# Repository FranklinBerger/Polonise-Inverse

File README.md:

# Calculatrice Polonaise Inversse

<p><strong>/!\ Projet en cours de développement vers une verssion stable et correctement doccumentée /!\</strong></p>

Commencé dans le cadre d'un mois de découverte de l'électronique, ce projet consiste en une calculatrice avec [notation en polonaise inversse](https://fr.wikipedia.org/wiki/Notation_polonaise_inverse) dont le hardware est propice à la découverte et l'initiation à l'électronique, soit:
* Montage
* Développement
* Mesures & Dépannage
* Programation

Basée sur ESP32 et dévelopée sur un firware [Micropython](https://github.com/micropython), elle est propice à une compréhenssion de sa structure fondamentale et à des réalisations pratique très rapidement

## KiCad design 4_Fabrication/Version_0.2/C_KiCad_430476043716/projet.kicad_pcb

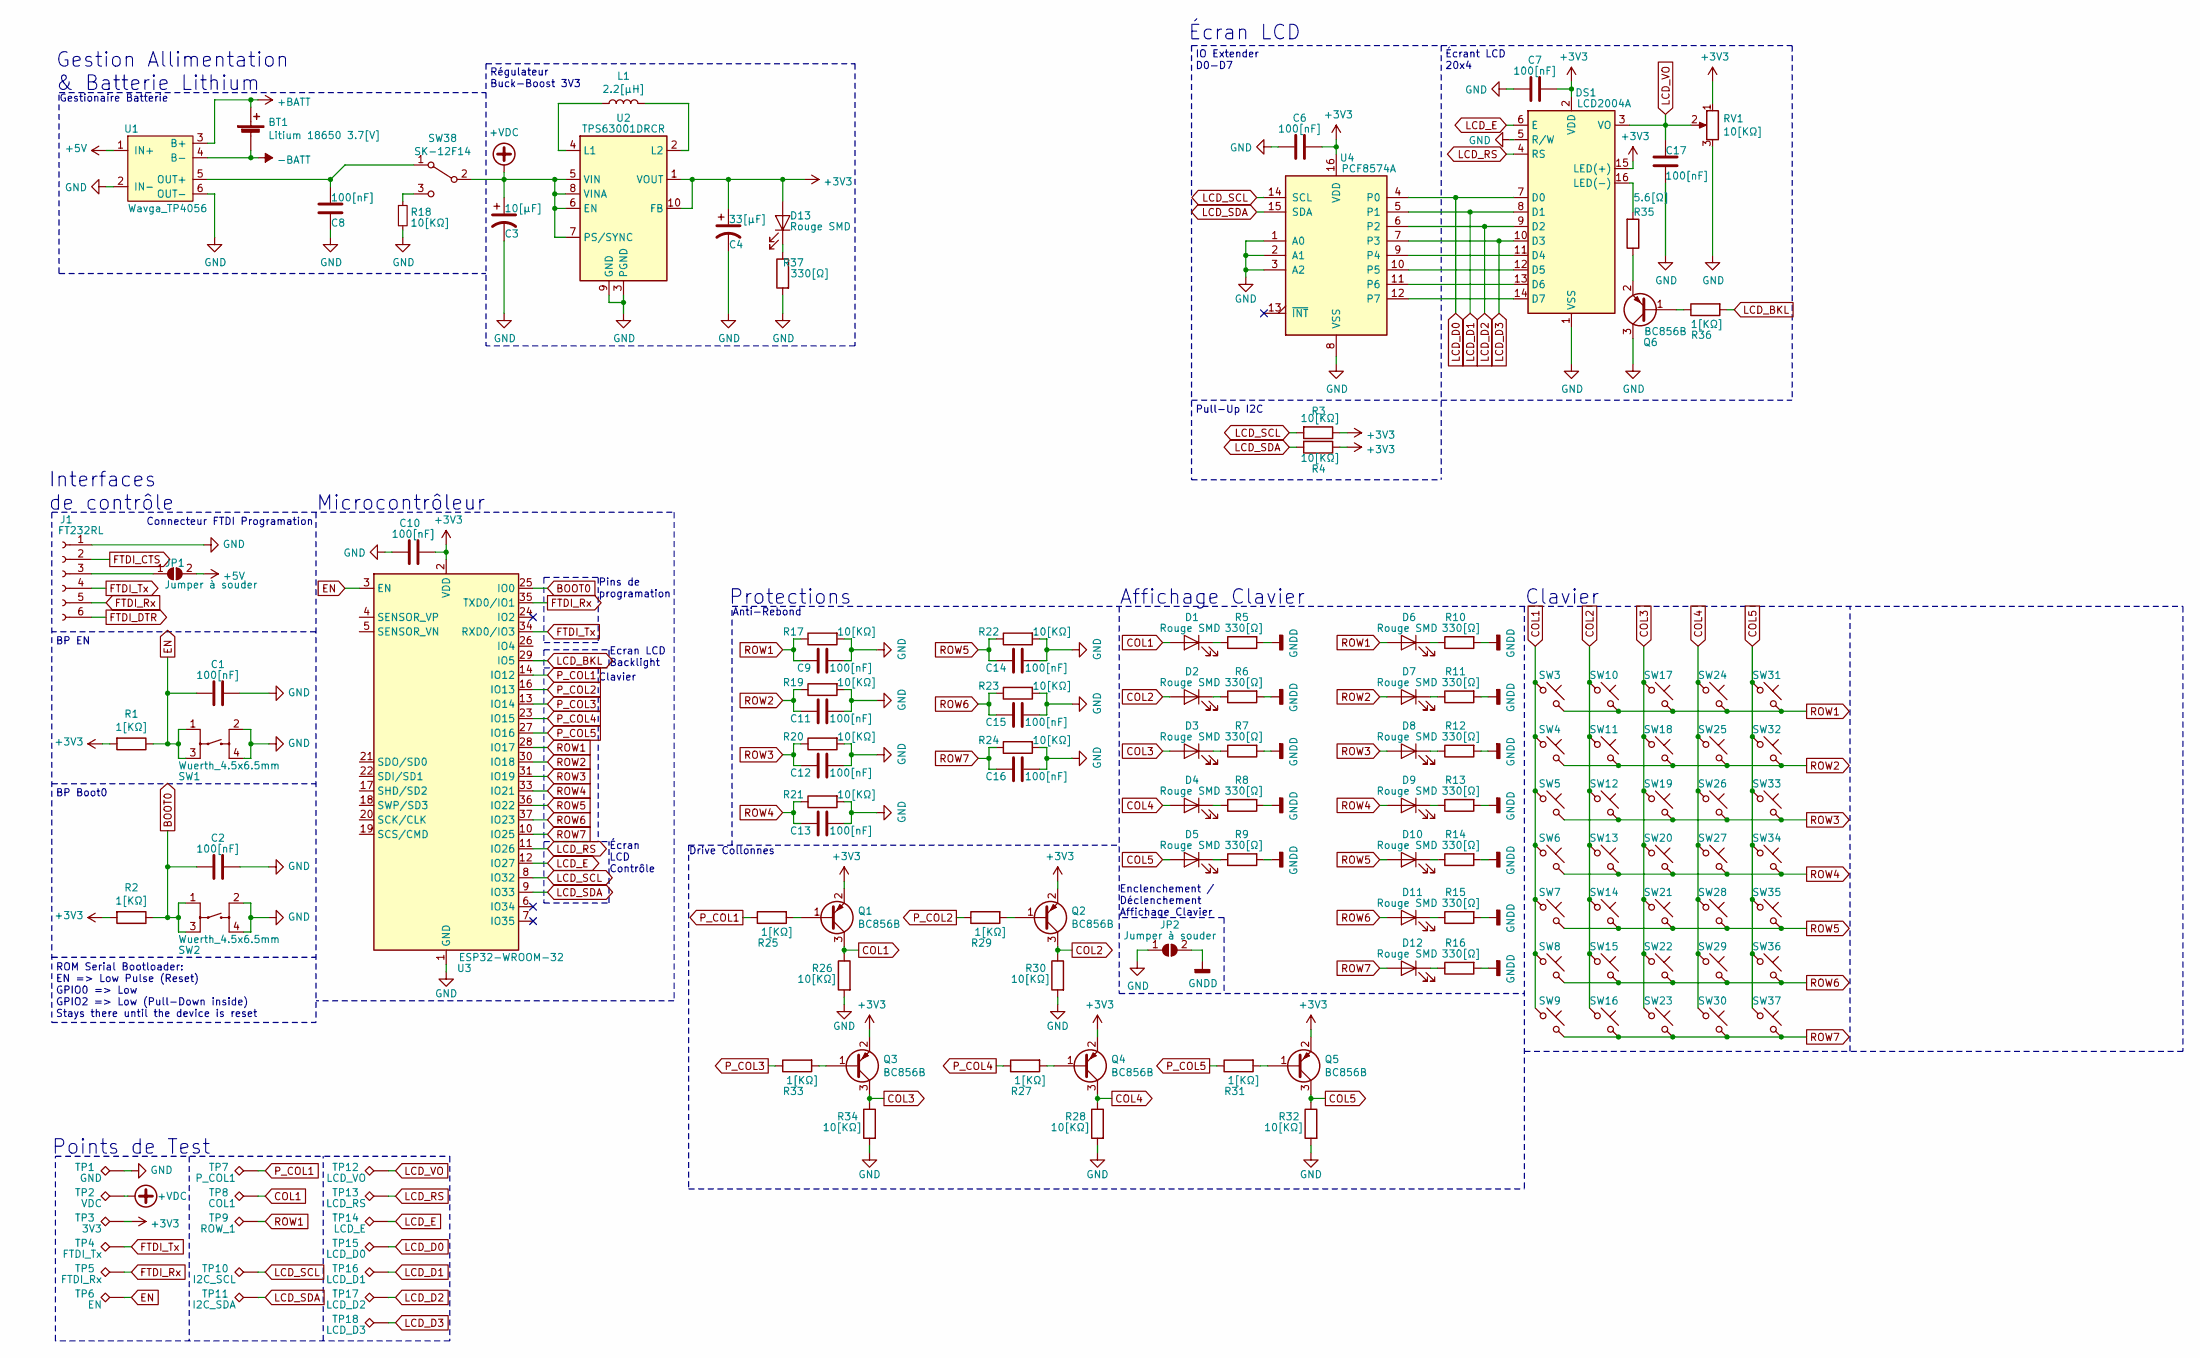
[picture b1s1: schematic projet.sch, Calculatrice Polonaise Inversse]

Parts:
BT1: Litium 18650 3.7[V]; BatteryHolder_Aliexpress_XZT_18650
C1, C2, C6, C7, C8, C9, C10, C11, C12, C13, C14, C15, C16, C17: 100[nF]; C_1206_3216Metric_Pad1.42x1.75mm_HandSolder
C3: 10[μF]; C_1206_3216Metric_Pad1.42x1.75mm_HandSolder
C4: 33[μF]; C_1206_3216Metric_Pad1.42x1.75mm_HandSolder
D1, D2, D3, D4, D5, D6, D7, D8, D9, D10, D11, D12, D13: Rouge SMD; LED_1206_3216Metric_ReverseMount_Hole1.8x2.4mm
DS1: LCD2004A; LCD2004A_TOP
J1: FT232RL; PinSocket_1x06_P2.54mm_Horizontal
JP1, JP2: Jumper à souder; SolderJumper-2_P1.3mm_Open_TrianglePad1.0x1.5mm
L1: 2.2[μH]; L_Taiyo-Yuden_NR-24xx_HandSoldering
Q1, Q2, Q3, Q4, Q5, Q6: BC856B; SOT-23_Handsoldering
R1, R2, R25, R27, R29, R31, R33, R36: 1[KΩ]; R_1206_3216Metric_Pad1.42x1.75mm_HandSolder
R3, R4, R17, R18, R19, R20, R21, R22, R23, R24, R26, R28, R30, R32, R34: 10[KΩ]; R_1206_3216Metric_Pad1.42x1.75mm_HandSolder
R5, R6, R7, R8, R9, R10, R11, R12, R13, R14, R15, R16, R37: 330[Ω]; R_1206_3216Metric_Pad1.42x1.75mm_HandSolder
R35: 5.6[Ω]; R_1206_3216Metric_Pad1.42x1.75mm_HandSolder
RV1: 10[KΩ]; Potentiometer_Bourns_3224J_Horizontal
SW1, SW2: Wuerth_4.5x6.5mm; SW_Wuerth_6.5x4.5mm
SW3, SW4, SW5, SW6, SW7, SW8, SW9, SW10, SW11, SW12, SW13, SW14, SW15, SW16, SW17, SW18, SW19, SW20, SW21, SW22, SW23, SW24, SW25, SW26, SW27, SW28, SW29, SW30, SW31, SW32, SW33, SW34, SW35, SW36, SW37: G77; SW_PUSH-12mm_Wuerth-430476085716
SW38: SK-12F14; SW_CuK_OS102011MA1QN1_SPDT_Angled
TP1: GND; TestPoint_Pad_1.5x1.5mm
TP2: VDC; TestPoint_Pad_1.5x1.5mm
TP3: 3V3; TestPoint_Pad_1.5x1.5mm
TP4: FTDI_Tx; TestPoint_Pad_1.5x1.5mm
TP5: FTDI_Rx; TestPoint_Pad_1.5x1.5mm
TP6: EN; TestPoint_Pad_1.5x1.5mm
TP7: P_COL1; TestPoint_Pad_1.5x1.5mm
TP8: COL1; TestPoint_Pad_1.5x1.5mm
TP9: ROW_1; TestPoint_Pad_1.5x1.5mm
TP10: I2C_SCL; TestPoint_Pad_1.5x1.5mm
TP11: I2C_SDA; TestPoint_Pad_1.5x1.5mm
TP12: LCD_VO; TestPoint_Pad_1.5x1.5mm
TP13: LCD_RS; TestPoint_Pad_1.5x1.5mm
TP14: LCD_E; TestPoint_Pad_1.5x1.5mm
TP15: LCD_D0; TestPoint_Pad_1.5x1.5mm
TP16: LCD_D1; TestPoint_Pad_1.5x1.5mm
TP17: LCD_D2; TestPoint_Pad_1.5x1.5mm
TP18: LCD_D3; TestPoint_Pad_1.5x1.5mm
U1: Wavga_TP4056; Wavgat_TP4056
U2: TPS63001DRCR; Texas_DRC0010J_ThermalVias
U3: ESP32-WROOM-32
U4: PCF8574A; SOIC-16W_7.5x10.3mm_P1.27mm

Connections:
+3V3: C4.1, C6.2, C7.2, C10.2, D13.2 (A), DS1.2 (VDD), DS1.15 (LED(+)), Q1.2 (E), Q2.2 (E), Q3.2 (E), Q4.2 (E), Q5.2 (E), R1.2, R2.2, R3.1, R4.1, RV1.1, TP3.1, U2.1 (VOUT), U2.10 (FB), U3.2 (VDD), U4.16 (VDD)
+5V: JP1.2 (B), U1.1 (IN+)
+BATT: BT1.1 (+), U1.3 (B+)
+VDC: C3.1, SW38.2 (B), TP2.1, U2.5 (VIN), U2.6 (EN), U2.7 (PS/SYNC), U2.8 (VINA)
-BATT: BT1.2 (-), U1.4 (B-)
BOOT0: C2.1, R2.1, SW2.1, SW2.3, U3.25 (IO0)
COL1: D1.2 (A), Q1.3 (C), R26.1, SW3.1, SW4.1, SW5.1, SW6.1, SW7.1, SW8.1, SW9.1, TP8.1
COL2: D2.2 (A), Q2.3 (C), R30.1, SW10.1, SW11.1, SW12.1, SW13.1, SW14.1, SW15.1, SW16.1
COL3: D3.2 (A), Q3.3 (C), R34.1, SW17.1, SW18.1, SW19.1, SW20.1, SW21.1, SW22.1, SW23.1
COL4: D4.2 (A), Q4.3 (C), R28.1, SW24.1, SW25.1, SW26.1, SW27.1, SW28.1, SW29.1, SW30.1
COL5: D5.2 (A), Q5.3 (C), R32.1, SW31.1, SW32.1, SW33.1, SW34.1, SW35.1, SW36.1, SW37.1
EN: C1.1, R1.1, SW1.1, SW1.3, TP6.1, U3.3 (EN)
FTDI_CTS: J1.2
FTDI_DTR: J1.6
FTDI_Rx: J1.5, TP5.1, U3.35 (TXD0/IO1)
FTDI_Tx: J1.4, TP4.1, U3.34 (RXD0/IO3)
GND: C1.2, C2.2, C3.2, C4.2, C6.1, C7.1, C8.2, C9.2, C10.1, C11.2, C12.2, C13.2, C14.2, C15.2, C16.2, C17.1, DS1.1 (VSS), DS1.5 (R/W), J1.1, JP2.1 (A), Q6.3 (C), R17.2, R18.2, R19.2, R20.2, R21.2, R22.2, R23.2, R24.2, R26.2, R28.2, R30.2, R32.2, R34.2, R37.2, RV1.3, SW1.2, SW1.4, SW2.2, SW2.4, TP1.1, U1.2 (IN-), U1.6 (OUT-), U2.3 (PGND), U2.9 (GND), U2.11 (PGND), U3.1 (GND), U3.15 (GND), U3.38 (GND), U3.39 (GND), U4.1 (A0), U4.2 (A1), U4.3 (A2), U4.8 (VSS)
GNDD: JP2.2 (B), R5.2, R6.2, R7.2, R8.2, R9.2, R10.2, R11.2, R12.2, R13.2, R14.2, R15.2, R16.2
LCD_BKL: R36.2, U3.29 (IO5)
LCD_D0: DS1.7 (D0), TP15.1, U4.4 (P0)
LCD_D1: DS1.8 (D1), TP16.1, U4.5 (P1)
LCD_D2: DS1.9 (D2), TP17.1, U4.6 (P2)
LCD_D3: DS1.10 (D3), TP18.1, U4.7 (P3)
LCD_E: DS1.6 (E), TP14.1, U3.12 (IO27)
LCD_RS: DS1.4 (RS), TP13.1, U3.11 (IO26)
LCD_SCL: R3.2, TP10.1, U3.8 (IO32), U4.14 (SCL)
LCD_SDA: R4.2, TP11.1, U3.9 (IO33), U4.15 (SDA)
LCD_VO: C17.2, DS1.3 (VO), RV1.2, TP12.1
unnamed: C8.1, SW38.1 (A), U1.5 (OUT+)
unnamed: D1.1 (K), R5.1
unnamed: D2.1 (K), R6.1
unnamed: D3.1 (K), R7.1
unnamed: D4.1 (K), R8.1
unnamed: D5.1 (K), R9.1
unnamed: D6.1 (K), R10.1
unnamed: D7.1 (K), R11.1
unnamed: D8.1 (K), R12.1
unnamed: D9.1 (K), R13.1
unnamed: D10.1 (K), R14.1
unnamed: D11.1 (K), R15.1
unnamed: D12.1 (K), R16.1
unnamed: D13.1 (K), R37.1
unnamed: DS1.11 (D4), U4.9 (P4)
unnamed: DS1.12 (D5), U4.10 (P5)
unnamed: DS1.13 (D6), U4.11 (P6)
unnamed: DS1.14 (D7), U4.12 (P7)
unnamed: DS1.16 (LED(-)), R35.2
unnamed: J1.3, JP1.1 (A)
unnamed: L1.1, U2.4 (L1)
unnamed: L1.2, U2.2 (L2)
unnamed: Q1.1 (B), R25.2
unnamed: Q2.1 (B), R29.2
unnamed: Q3.1 (B), R33.2
unnamed: Q4.1 (B), R27.2
unnamed: Q5.1 (B), R31.2
unnamed: Q6.1 (B), R36.1
unnamed: Q6.2 (E), R35.1
unnamed: R18.1, SW38.3 (C)
P_COL1: R25.1, TP7.1, U3.14 (IO12)
P_COL2: R29.1, U3.16 (IO13)
P_COL3: R33.1, U3.13 (IO14)
P_COL4: R27.1, U3.23 (IO15)
P_COL5: R31.1, U3.27 (IO16)
ROW1: C9.1, D6.2 (A), R17.1, SW3.2, SW10.2, SW17.2, SW24.2, SW31.2, TP9.1, U3.28 (IO17)
ROW2: C11.1, D7.2 (A), R19.1, SW4.2, SW11.2, SW18.2, SW25.2, SW32.2, U3.30 (IO18)
ROW3: C12.1, D8.2 (A), R20.1, SW5.2, SW12.2, SW19.2, SW26.2, SW33.2, U3.31 (IO19)
ROW4: C13.1, D9.2 (A), R21.1, SW6.2, SW13.2, SW20.2, SW27.2, SW34.2, U3.33 (IO21)
ROW5: C14.1, D10.2 (A), R22.1, SW7.2, SW14.2, SW21.2, SW28.2, SW35.2, U3.36 (IO22)
ROW6: C15.1, D11.2 (A), R23.1, SW8.2, SW15.2, SW22.2, SW29.2, SW36.2, U3.37 (IO23)
ROW7: C16.1, D12.2 (A), R24.1, SW9.2, SW16.2, SW23.2, SW30.2, SW37.2, U3.10 (IO25)

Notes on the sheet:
Gestion Allimentation & Batterie Lithium
Gestionaire Batterie
Régulateur Buck-Boost 3V3
BP EN
BP Boot0
Connecteur FTDI Programation
Interfaces de contrôle
Pins de programation
ROM Serial Bootloader: EN => Low Pulse (Reset) GPIO0 => Low GPIO2 => Low (Pull-Down inside) Stays there until the device is reset
Clavier
Écran LCD Contrôle
Microcontrôleur
Affichage Clavier
Enclenchement / Déclenchement Affichage Clavier
IO Extender D0-D7
Écrant LCD 20x4
Pull-Up I2C
Écran LCD
Protections
Anti-Rebond
Drive Collonnes
Points de Test
Ecran LCD Backlight

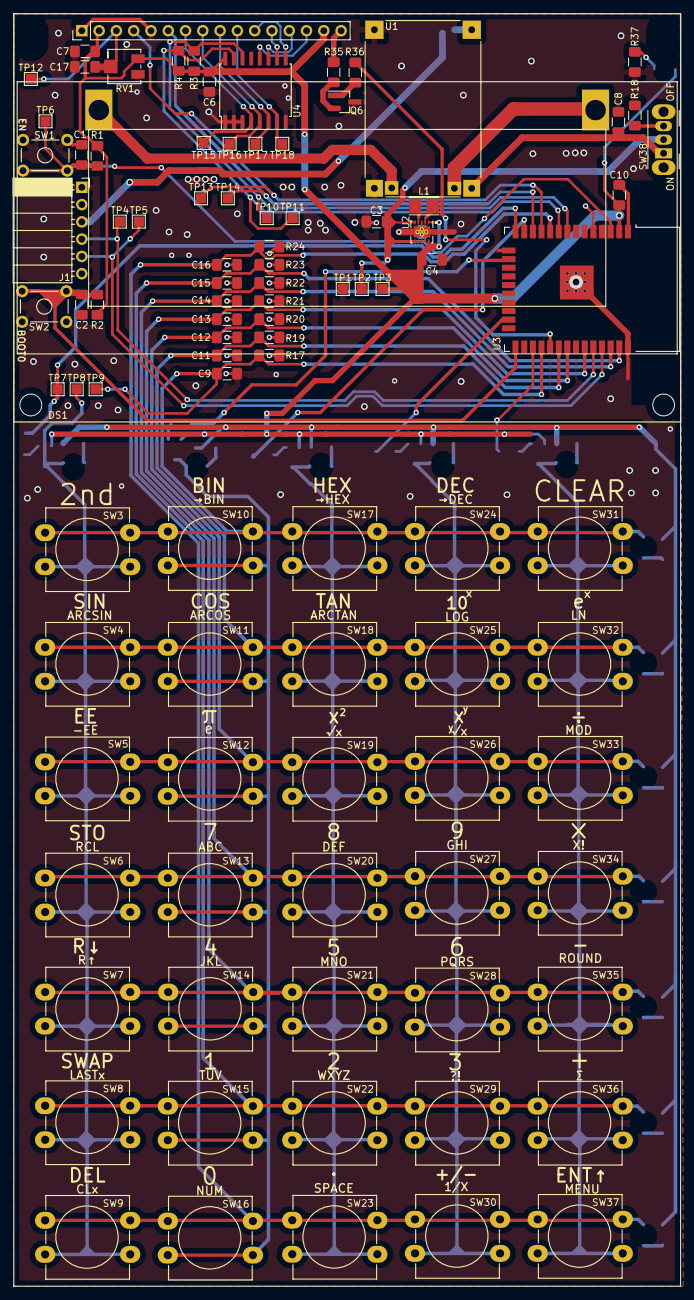
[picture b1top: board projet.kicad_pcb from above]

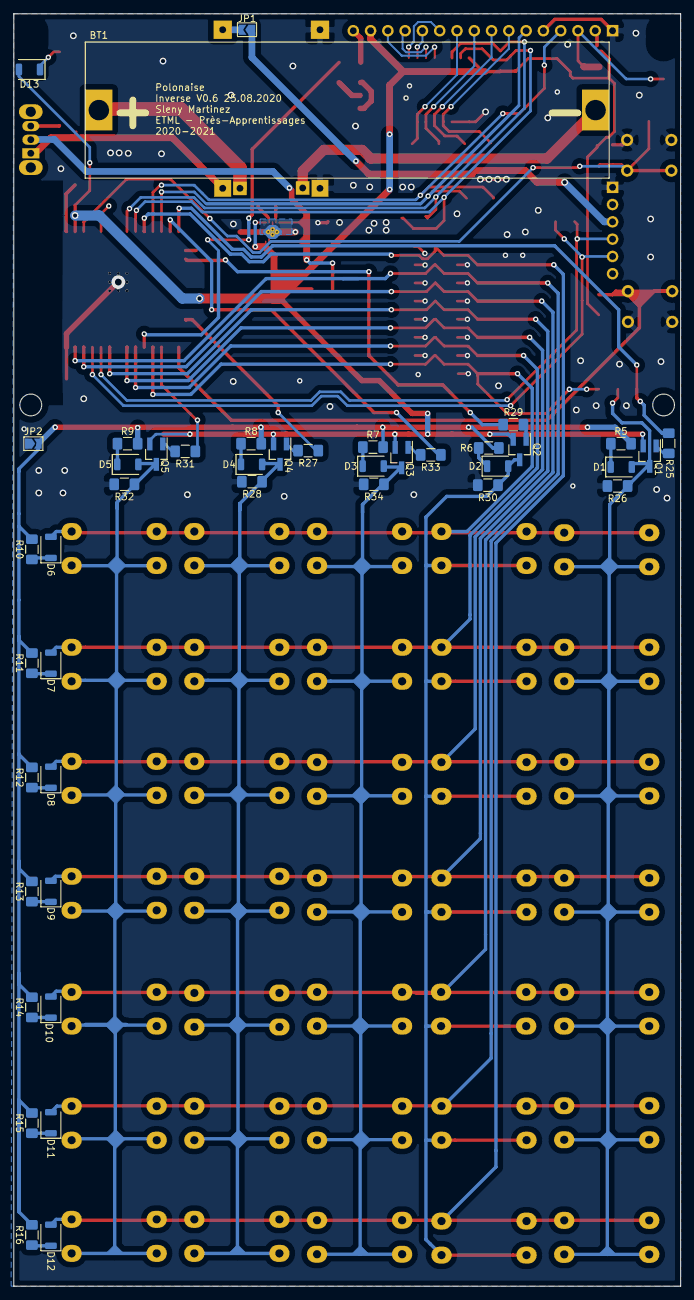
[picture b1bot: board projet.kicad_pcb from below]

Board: 2 copper layers, 98.0 x 187.0 mm, 139 parts (43 on the bottom side), 68 nets.

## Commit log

2019-06-04 firts synchro
    permeère synchro
2019-06-04 Création projet KiCad
2020-08-24 24.08.2020
2020-08-24 Clavier
2020-08-25 Commande PCD 25.08.2020 midi
2020-08-25 Soir 25.08.2020
2020-09-04 04.05.2020
2020-09-04 remove large file
2020-09-16 Writing Code
2020-09-16 près-mplab
2020-09-18 Implemeting opperations
2020-09-22 Developing RPN
2020-09-22 Correcting for last version of HW
2020-09-24 Constant & Debug structure
2020-10-09 MAJ Hardware
2021-01-11 Minior Edits
2021-01-22 Code complet: V1.0
    Publication de la première verssion complète du code (V1.0)
2021-01-22 Mise sous ZIP du HTML
    Mise sous zip des importants fichiers HTML de documentation
2021-01-22 ZIPZIPZIP
2021-07-02 Last version of code
